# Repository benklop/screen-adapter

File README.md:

# 720x720 DSI Display (FL7707N Controller)

## Overview

This directory contains documentation and configuration files for supporting a 720x720 DSI display with FL7707N controller.

**Product Link**: [AliExpress - 720x720 DSI Display](https://www.aliexpress.us/item/3256807565141061.html)

**IMPORTANT**: This specific display module does NOT include touch hardware. While GT911 touch controller documentation is provided for reference, the current implementation focuses solely on display output. The PicoCalc hardware would require modifications to support touchscreen functionality.

## Specifications

- **Resolution**: 720x720 pixels
- **Panel Type**: IPS
- **Interface**: 2-lane MIPI DSI
- **Display Controller**: FL7707N
- **Touch Controller**: None (display-only module)

**Note**: While GT911 touch controller configuration is available in the documentation, this specific display module does not include touch hardware.

## Display Timing Parameters

```
Width:  720
Height: 720

Vertical Timing:
- VFP: 20 (Vertical Front Porch)
- VBP: 20 (Vertical Back Porch) 
- VSA: 4  (Vertical Sync Active)

Horizontal Timing:
- HFP: 106 (Horizontal Front Porch)
- HBP: 120 (Horizontal Back Porch)
- HSA: 60  (Horizontal Sync Active)
```

## Files

### Display Controller Documentation
- `2_FL7707N_QV040YNQ-N80_IPS_Code_2Power_V5.5_20230810.txt` - Display initialization sequence and timing configuration
- `FL7707N_DS_V0.2_20230324_Customer.pdf` - FL7707N display controller datasheet and specifications

### Display Module Documentation  
- `HD395003C30-V2 规格书.pdf` - Display module specifications
- `HD395003C30工程图20231023.dwg` - Engineering drawings and mechanical specifications (AutoCAD format)

### Touch Controller Configuration (Reference Only)
- `../../touch/FT040037_GT911_Config_20231103.cfg` - GT911 touch controller configuration (not applicable to current display samples - no touch panel)

## DSI Configuration

- **DSI Mode**: 2-lane (0x31 in register 0xBA[1])
- **Power Mode**: 2-power configuration
- **Color Format**: RGB888

## Implementation Status

- [x] Device tree overlay creation
- [x] Display driver implementation
- [x] Timing parameter configuration
- [x] Power sequence setup
- [ ] Testing and validation

## Notes

The initialization sequence includes:
- Power management configuration (B8 register for 2-power mode)
- DSI lane configuration (BA register)
- Gamma correction settings (E0 register)
- GIP (Gate In Panel) timing configuration (E9/EA registers)
- Touch controller I2C configuration

## Adapter

In order to connect the display to the Lyra, you need will to construct an adapter with the following pinout:
| Lyra Pin # | Display Pin # | Signal Name      | Description                       | Connection               |
|------------|---------------|------------------|-----------------------------------|--------------------------|
| 4          | 1             | LEDK             | Backlight Cathode                 | (See circuit)            |
| 4          | 2             | LEDK             | Backlight Cathode                 | (See circuit)            |
| 6          | 3             | LEDA             | Backlight Anode                   | (See circuit)            |
| 4          | 4             | GND              | Ground                            | GND                      |
| 5          | 5             | RST              | Reset Input Pin                   | GPIO1_C4                 |
| 7          | 6             | GND              | Ground                            | GND                      |
| 1          | 7             | VCC              | Power Supply 2.8V-3.3V            | VCC                      |
| 7          | 8             | GND              | Ground                            | GND                      |
| 1          | 9             | IOVCC            | Power Supply 1.8V-3.3V            | VCC                      |
| 10         | 10            | GND              | Ground                            | GND                      |
| 20         | 11            | D0P              | MIPI DSI Data Lane 0 Positive     | DSI_TX_D0_P              |
| 21         | 12            | D0N              | MIPI DSI Data Lane 0 Negative     | DSI_TX_D0_N              |
| 13         | 13            | GND              | Ground                            | GND                      |
| 17         | 14            | D1P              | MIPI DSI Data Lane 1 Positive     | DSI_TX_D1_P              |
| 18         | 15            | D1N              | MIPI DSI Data Lane 1 Negative     | DSI_TX_D1_N              |
| 16         | 16            | GND              | Ground                            | GND                      |
| 14         | 17            | CLKP             | MIPI DSI Clock Lane Positive      | DSI_TX_CLK_P             |
| 15         | 18            | CLKN             | MIPI DSI Clock Lane Negative      | DSI_TX_CLK_N             |
| 19         | 19            | GND              | Ground                            | GND                      |
| 19         | 20            | GND              | Ground                            | GND                      |
| 19         | 21            | GND              | Ground                            | GND                      |
| 22         | 22            | GND              | Ground                            | GND                      |
| 22         | 23            | GND              | Ground                            | GND                      |
| 22         | 24            | GND              | Ground                            | GND                      |
| NC         | 25            | TP_INT           | Touchpad                          | N.C.                     |
| 2          | 26            | TP_SDA           | Touchpad / BL I2C                 | GPIO0_A0 RMIO_0 I2C2_SDA |
| 3          | 27            | TP_SCL           | Touchpad / BL I2C                 | GPIO0_A1 RMIO_1 I2C2_SCL |
| NC         | 28            | TP_RST           | Touchpad                          | GPIO1_C4                 |
| NC         | 29            | TP_VCI           | Touchpad                          | VCC                      |
| NC         | 30            | GND              | Ground                            |                          |

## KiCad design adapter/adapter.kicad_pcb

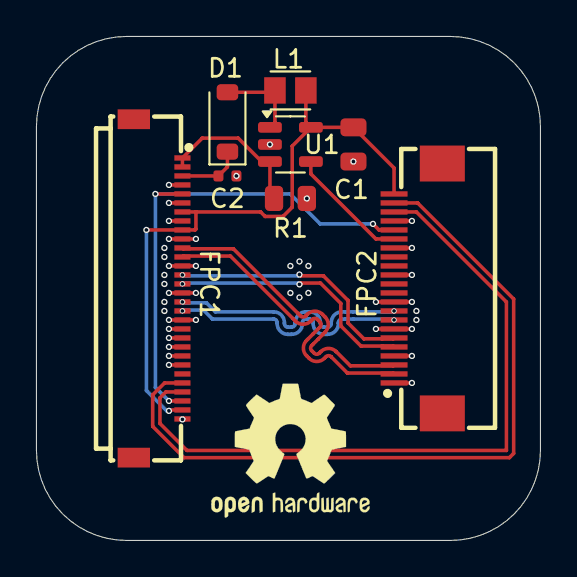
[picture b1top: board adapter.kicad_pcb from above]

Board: 4 copper layers, 28.0 x 28.0 mm, 8 parts (0 on the bottom side), 15 nets.

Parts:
C1: 4.7uF; C_0805
C2: 1uF; C_0402
D1: MBR0530; D_SOD-123
FPC1: FPC-05F-30PH15; FPC-SMD_30P-P0.50_XUNPU_FPC-05F-30PH15
FPC2: FPC-05F-22PH20; FPC-SMD_22P-P0.50_FPC-05F-22PH20
L1: MLZ2012N100LT000; INDC2012X145N
R1: 33Ω; R_0805
U1: TPS61041DBV; SOT-23-5

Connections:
/ANODE: C2.1, D1.1 (K), FPC1.3
/CATHODE: FPC1.1, FPC1.2, R1.2, U1.3 (FB)
/DSI_0_N: FPC1.12, FPC2.2
/DSI_0_P: FPC1.11, FPC2.3
/DSI_1_N: FPC1.15, FPC2.5
/DSI_1_P: FPC1.14, FPC2.6
/DSI_CLK_N: FPC1.18, FPC2.8
/DSI_CLK_P: FPC1.17, FPC2.9
/PWM: FPC2.17, U1.4 (EN)
/RESET: FPC1.5, FPC1.28, FPC2.18
/SCL: FPC1.27, FPC2.20
/SDA: FPC1.26, FPC2.21
/VCC: C1.1, FPC1.7, FPC1.9, FPC1.29, FPC2.22, L1.1, U1.5 (VIN)
GND: C1.2, C2.2, FPC1.4, FPC1.6, FPC1.8, FPC1.10, FPC1.13, FPC1.16, FPC1.19, FPC1.20, FPC1.21, FPC1.22, FPC1.23, FPC1.24, FPC1.30, FPC2.1, FPC2.4, FPC2.7, FPC2.10, FPC2.13, FPC2.16, FPC2.19, R1.1, U1.2 (GND)
unnamed: D1.2 (A), L1.2, U1.1 (SW)

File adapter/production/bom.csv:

Designator,Footprint,Quantity,Value,LCSC Part #
C1,C_0805,1,4.7uF,C1779
C2,C_0402,1,1uF,C52923
D1,D_SOD-123,1,MBR0530,
FPC1,FPC-SMD_30P-P0.50_XUNPU_FPC-05F-30PH15,1,FPC-05F-30PH15,C2856824
FPC2,FPC-SMD_22P-P0.50_FPC-05F-22PH20,1,FPC-05F-22PH20,C2856804
L1,INDC2012X145N,1,MLZ2012N100LT000,
R1,R_0805,1,33Ω,C17634
U1,SOT-23-5,1,TPS61041DBV,
